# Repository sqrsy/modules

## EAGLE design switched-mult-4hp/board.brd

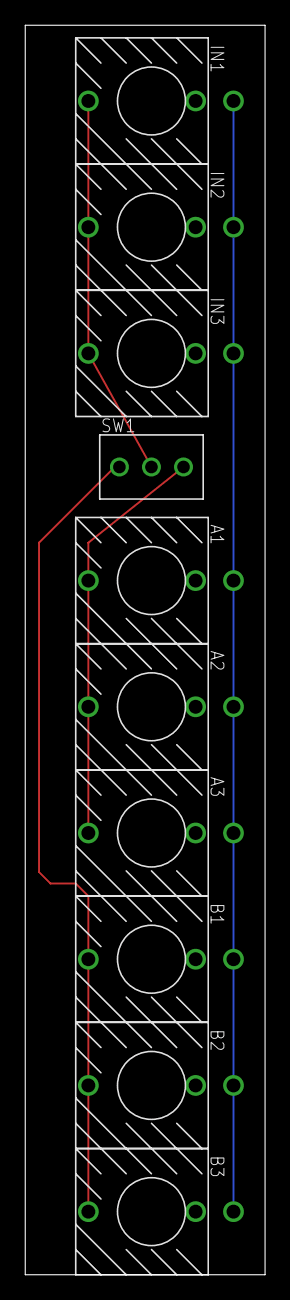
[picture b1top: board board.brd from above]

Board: 2 copper layers, 19.0 x 99.0 mm, 10 parts (0 on the bottom side), 4 nets.

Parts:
A1, A2, A3: THONKI-STEREO; WQP-PJ366ST_JACK
B1, B2, B3: THONKI-STEREO; WQP-PJ366ST_JACK
IN1, IN2, IN3: THONKI-STEREO; WQP-PJ366ST_JACK
SW1: SUBMINI_SPDT; SUBMINI_TOGGLE

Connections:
unnamed: A1.P$1_TIP, A2.P$1_TIP, A3.P$1_TIP, SW1.3
unnamed: B1.P$1_TIP, B2.P$1_TIP, B3.P$1_TIP, SW1.1
unnamed: IN1.P$1_TIP, IN2.P$1_TIP, IN3.P$1_TIP, SW1.COM
unnamed: A1.P$3_SLEEVE, A2.P$3_SLEEVE, A3.P$3_SLEEVE, B1.P$3_SLEEVE, B2.P$3_SLEEVE, B3.P$3_SLEEVE, IN1.P$3_SLEEVE, IN2.P$3_SLEEVE, IN3.P$3_SLEEVE

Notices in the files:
switched-mult-4hp/board.brd:
TAPR OPEN HARDWARE LICENSE
